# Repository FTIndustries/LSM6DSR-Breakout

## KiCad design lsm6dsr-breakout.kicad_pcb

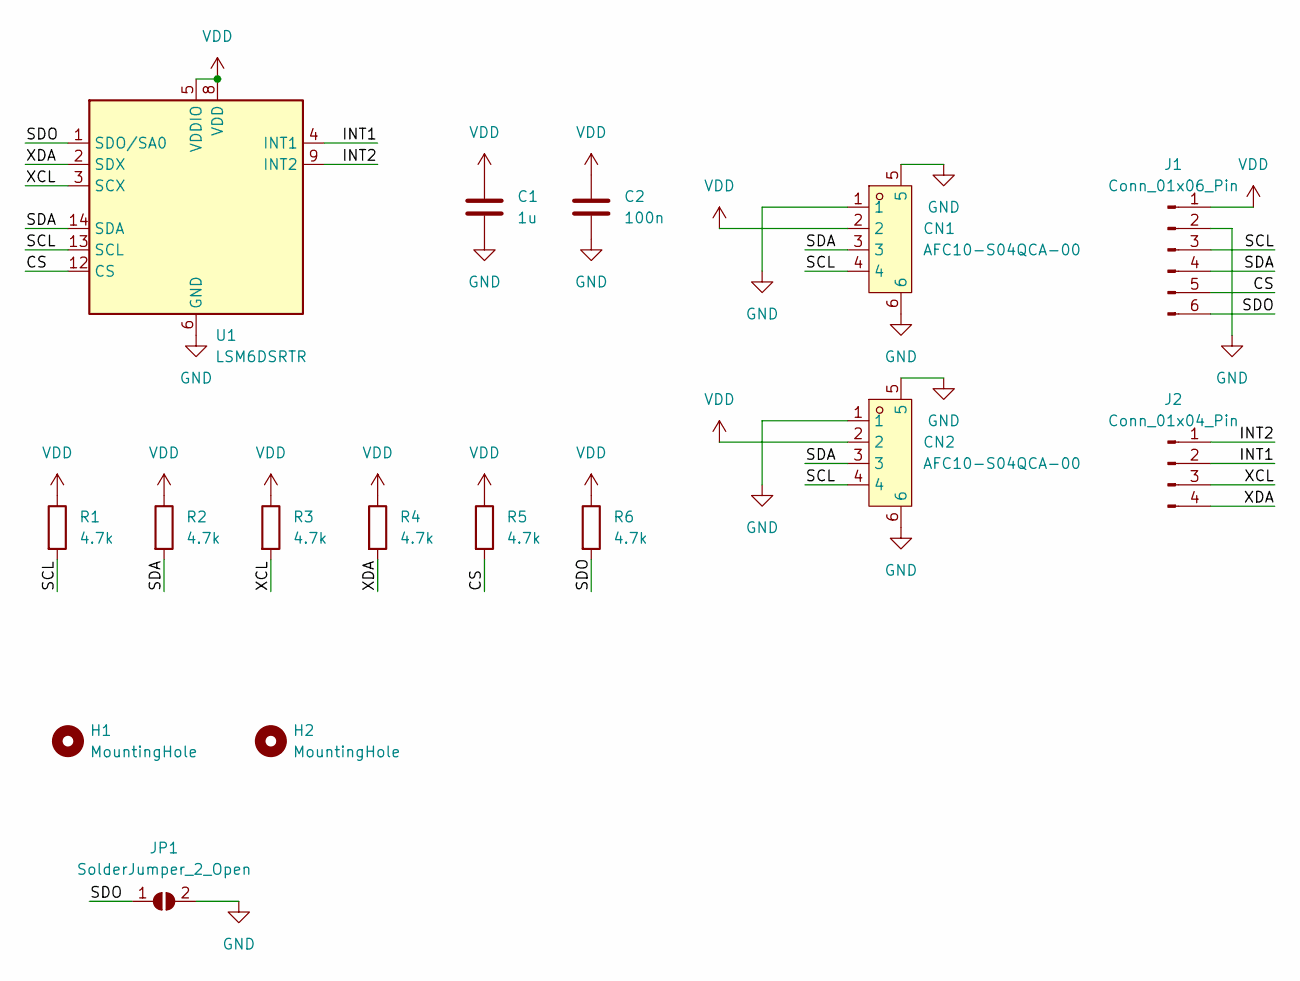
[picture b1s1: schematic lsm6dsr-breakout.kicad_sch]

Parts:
C1: 1u; C_0603_1608Metric
C2: 100n; C_0402_1005Metric
CN1, CN2: AFC10-S04QCA-00; CONN-SMD_AFC10-S04QCA-00; LCSC Part C2764183
H1, H2: MountingHole; MountingHole_2.2mm_M2
J1: Conn_01x06_Pin; PinHeader_1x06_P2.54mm_Vertical
J2: Conn_01x04_Pin; PinHeader_1x04_P2.54mm_Vertical
JP1: SolderJumper_2_Open; SolderJumper-2_P1.3mm_Open_TrianglePad1.0x1.5mm
R1, R2, R3, R4, R5, R6: 4.7k; R_0402_1005Metric
U1: LSM6DSRTR; LGA-14_3x2.5mm_P0.5mm_LayoutBorder3x4y

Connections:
/CS: J1.5, R5.2, U1.12 (CS)
/INT1: J2.2, U1.4 (INT1)
/INT2: J2.1, U1.9 (INT2)
/SCL: CN1.4, CN2.4, J1.3, R1.2, U1.13 (SCL)
/SDA: CN1.3, CN2.3, J1.4, R2.2, U1.14 (SDA)
/SDO: J1.6, JP1.1 (A), R6.2, U1.1 (SDO/SA0)
/XCL: J2.3, R3.2, U1.3 (SCX)
/XDA: J2.4, R4.2, U1.2 (SDX)
GND: C1.2, C2.2, CN1.1, CN1.5, CN1.6, CN2.1, CN2.5, CN2.6, J1.2, JP1.2 (B), U1.6 (GND), U1.7 (GND)
VDD: C1.1, C2.1, CN1.2, CN2.2, J1.1, R1.1, R2.1, R3.1, R4.1, R5.1, R6.1, U1.5 (VDDIO), U1.8 (VDD)

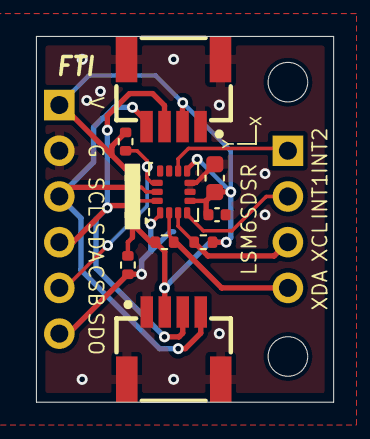
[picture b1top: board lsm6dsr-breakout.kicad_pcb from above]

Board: 2 copper layers, 16.5 x 20.3 mm, 16 parts (1 on the bottom side), 10 nets.

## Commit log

2024-04-23 ASDFSAFSDF
2024-04-23 readme del
2024-05-10 gitignore
2024-05-19 beautify schematic
2024-12-02 use higher pullups, make it dippable, comply MEMS design guideline
